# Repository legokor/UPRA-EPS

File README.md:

# UPRA-EPS
UPRA Electric Power(distributon) Subsystem
----
This subsystem provides the designated voltage levels for other subsystems and payloads, monitors power consumption, battery charge, battery temperature and switch off malfunctioned modules.

UPRA-EPS is connected to the system via UPRA-BUS, provides house-keeping and full power control over the subsystems and supports RBF start pin and DSW Switch for future cubesat applications.

## Hardware
In the Hardware folder the schematic and PCB design can be found. The hardware is AVR 8-bit (Arduino) based, later versions might upgraded to ARM based solutions.

## Firmware
The Firmware folder contains the embedded software for the UPRA-EPS for power distribution control, monitoring and internal communication.

## Battery Tester
The Battery_tester folder contains the hardware and software design of the test equipment to determine characteristics of different battery configurations. Results can be found at the Wiki section.

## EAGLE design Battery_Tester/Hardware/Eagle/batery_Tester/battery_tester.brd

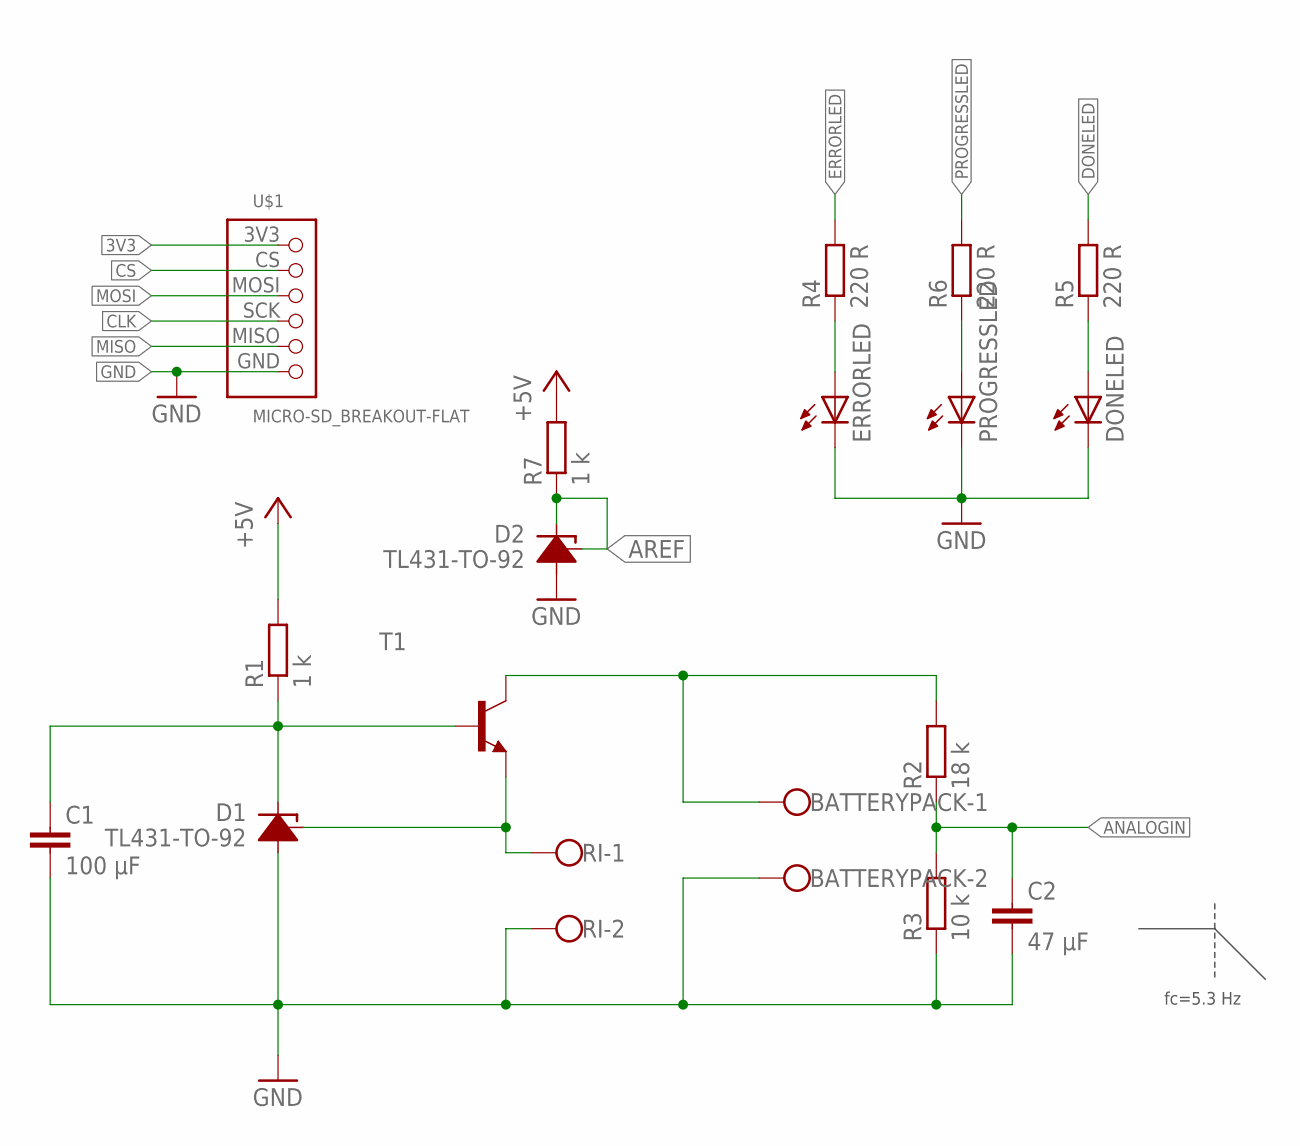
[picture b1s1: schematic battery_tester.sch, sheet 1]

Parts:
BATTERYPACK: W237-102
C1: 100 µF; C1206
C2: 47 µF; C1206
D1, D2: TL431-TO-92; TO-92
DONELED: LEDSML1206; SML1206
ERRORLED: LEDSML1206; SML1206
PROGRESSLED: LEDSML1206; SML1206
R1, R7: 1 k; R1206
R2: 18 k; R1206
R3: 10 k; R1206
R4, R5, R6: 220 R; R1206
RI: W237-102
T1: -NPN-TO92; TO92
U$1: MICRO-SD_BREAKOUT-FLAT; MICRO-SD_BREAKOUT_FLAT

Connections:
3V3: U$1.3V3; also elsewhere on the board
+5V: R1.2, R7.2; also elsewhere on the board
ANALOGIN: C2.1, R2.1, R3.2; also elsewhere on the board
AREF: D2.1 (J), D2.3 (K), R7.1; also elsewhere on the board
BATTERYPACK+: BATTERYPACK.1, R2.2, T1.3 (C)
CLK: U$1.SCK; also elsewhere on the board
CS: U$1.CS; also elsewhere on the board
DONELED: R5.2; also elsewhere on the board
ERRORLED: R4.2; also elsewhere on the board
GND: BATTERYPACK.2, C1.2, C2.2, D1.2 (A), D2.2 (A), DONELED.C, ERRORLED.C, PROGRESSLED.C, R3.1, RI.2, U$1.GND; also elsewhere on the board
MISO: U$1.MISO; also elsewhere on the board
MOSI: U$1.MOSI; also elsewhere on the board
unnamed: C1.1, D1.3 (K), R1.1, T1.2 (B)
unnamed: ERRORLED.A, R4.1
unnamed: D1.1 (J), RI.1, T1.1 (E)
unnamed: PROGRESSLED.A, R6.1
unnamed: DONELED.A, R5.1
PROGRESSLED: R6.2; also elsewhere on the board

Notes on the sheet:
fc=5.3 Hz

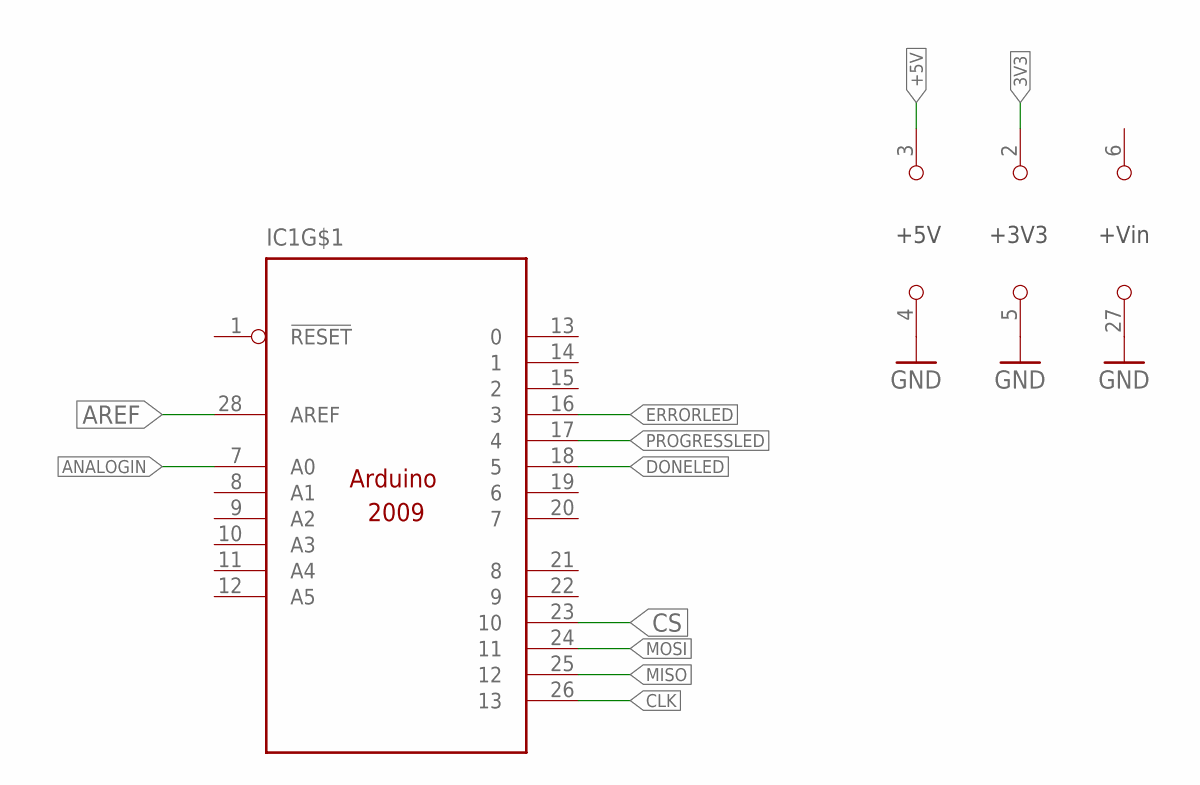
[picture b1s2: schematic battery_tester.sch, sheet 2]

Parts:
IC1: ARDUINO2009_22; ARDUINO2009_2

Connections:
3V3: IC1.2 (+3V3); also elsewhere on the board
+5V: IC1.3 (+5V); also elsewhere on the board
+VIN: IC1.6 (+VIN)
ANALOGIN: IC1.7 (A0); also elsewhere on the board
AREF: IC1.28 (AREF); also elsewhere on the board
CLK: IC1.26 (13); also elsewhere on the board
CS: IC1.23 (10); also elsewhere on the board
DONELED: IC1.18 (5); also elsewhere on the board
ERRORLED: IC1.16 (3); also elsewhere on the board
GND: IC1.4 (GND), IC1.5 (GND), IC1.27 (GND); also elsewhere on the board
MISO: IC1.25 (12); also elsewhere on the board
MOSI: IC1.24 (11); also elsewhere on the board
PROGRESSLED: IC1.17 (4); also elsewhere on the board

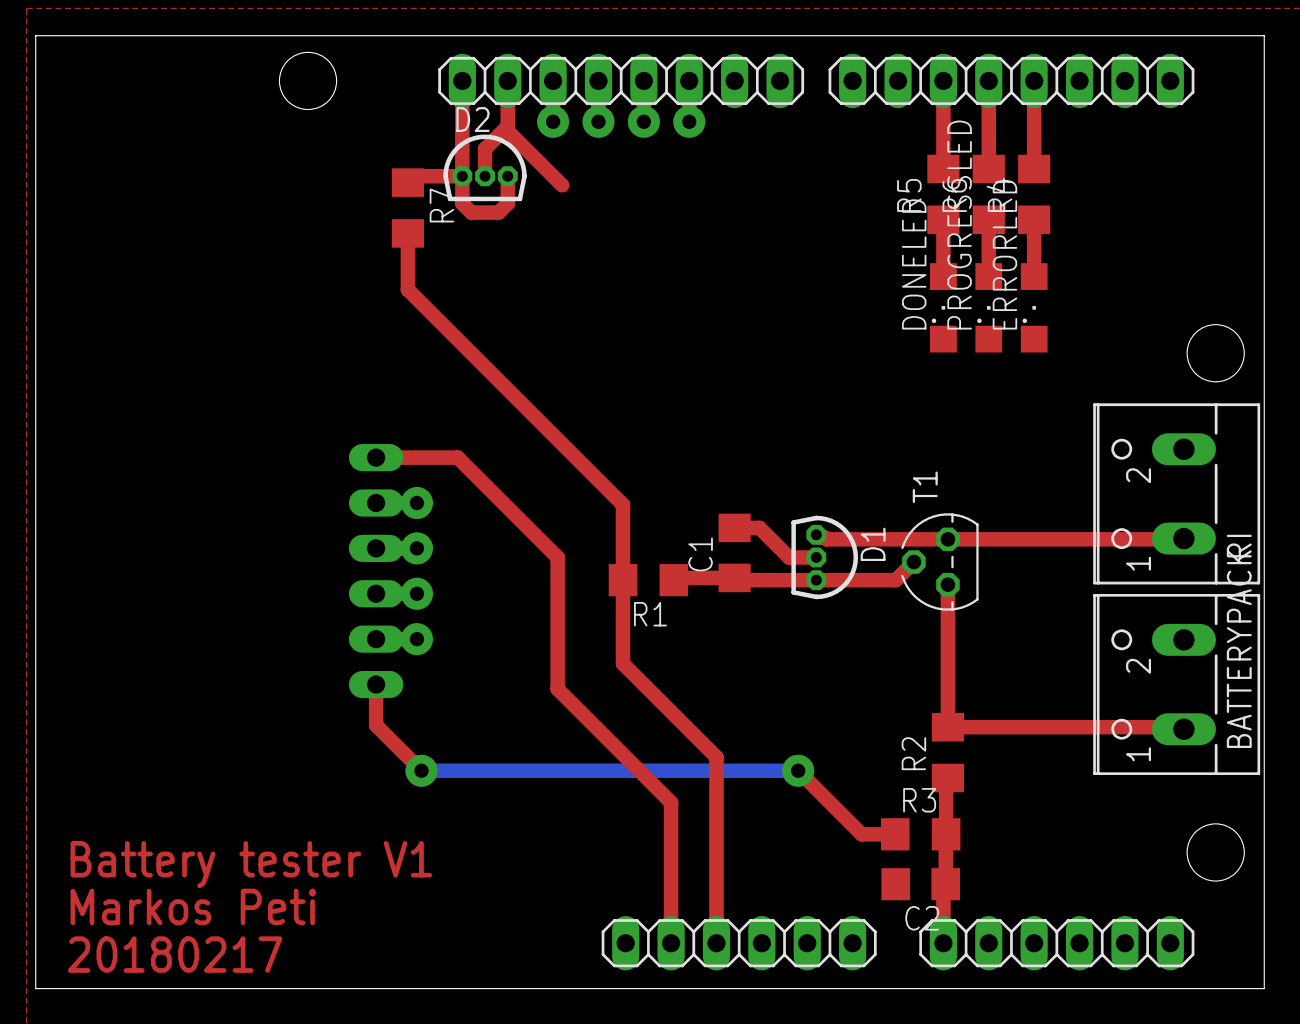
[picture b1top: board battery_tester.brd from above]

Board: 2 copper layers, 68.8 x 53.3 mm, 19 parts (1 on the bottom side), 18 nets.

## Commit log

2017-11-12 README.md updated
2017-11-12 README.md created
2017-11-12 Schematic Added
    Battery Tester basic schematic added in Eagle format
2017-11-25 Schematic values updated
    For Issue #10
